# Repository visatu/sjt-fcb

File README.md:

View this project on [CADLAB.io](https://cadlab.io/project/25264).

**PRELIMINARY DESIGN - NOT TESTED - YET**

# sjt-fcb

Drone flight controller designed for hobbyist use. Designed as a part of an embedded design course.

## Features

| Component     | Desc                                                                                                                                                                                                |
| ------------- | --------------------------------------------------------------------------------------------------------------------------------------------------------------------------------------------------- |
| CPU           | [ST STM32F411CEU6](https://www.st.com/resource/en/datasheet/stm32f411ce.pdf)                                                                                                                        |
| IMU           | [ST LSM6DS3](https://content.arduino.cc/assets/st_imu_lsm6ds3_datasheet.pdf)                                                                                                                        |
| Onboard flash | 128 Mb SPI NOR                                                                                                                                                                                      |
| RF Module     | [SiLabs SI4432](https://www.silabs.com/documents/public/data-sheets/Si4430-31-32.pdf) based 315 - 915 MHz [module](https://datasheet.lcsc.com/lcsc/1912111437_DreamLNK-DL-RTS4432-433M_C381165.pdf) |
| Barometer     | [Infineon DPS310](https://www.infineon.com/dgdl/Infineon-DPS310-DataSheet-v01_02-EN.pdf?fileId=5546d462576f34750157750826c42242)                                                                    |
| Magnetometer  | [QST QMC5883L ](https://datasheet.lcsc.com/lcsc/2012221837_QST-QMC5883L_C976032.pdf)                                                                                                                |
|               |                                                                                                                                                                                                     |

- Designed to connect to a
[RaceStar 35A](https://www.racerstar.com/Anniversary-Special-Edition-Racerstar-REV35-35A-BLheli_S-3-6S-4-In-1-ESC-Built-in-Current-Sensor-for-RC-Drone-p-254.html) ESC
- 2.0 mm pitch connectors for external I/O
  - I2C
  - UART
  - 2 x 5V Analog input
  - 1 x 3V Analog input
  - 2 x GPIO
- USB 2.0 connection
- Onboard buzzer
- User programmable button :)

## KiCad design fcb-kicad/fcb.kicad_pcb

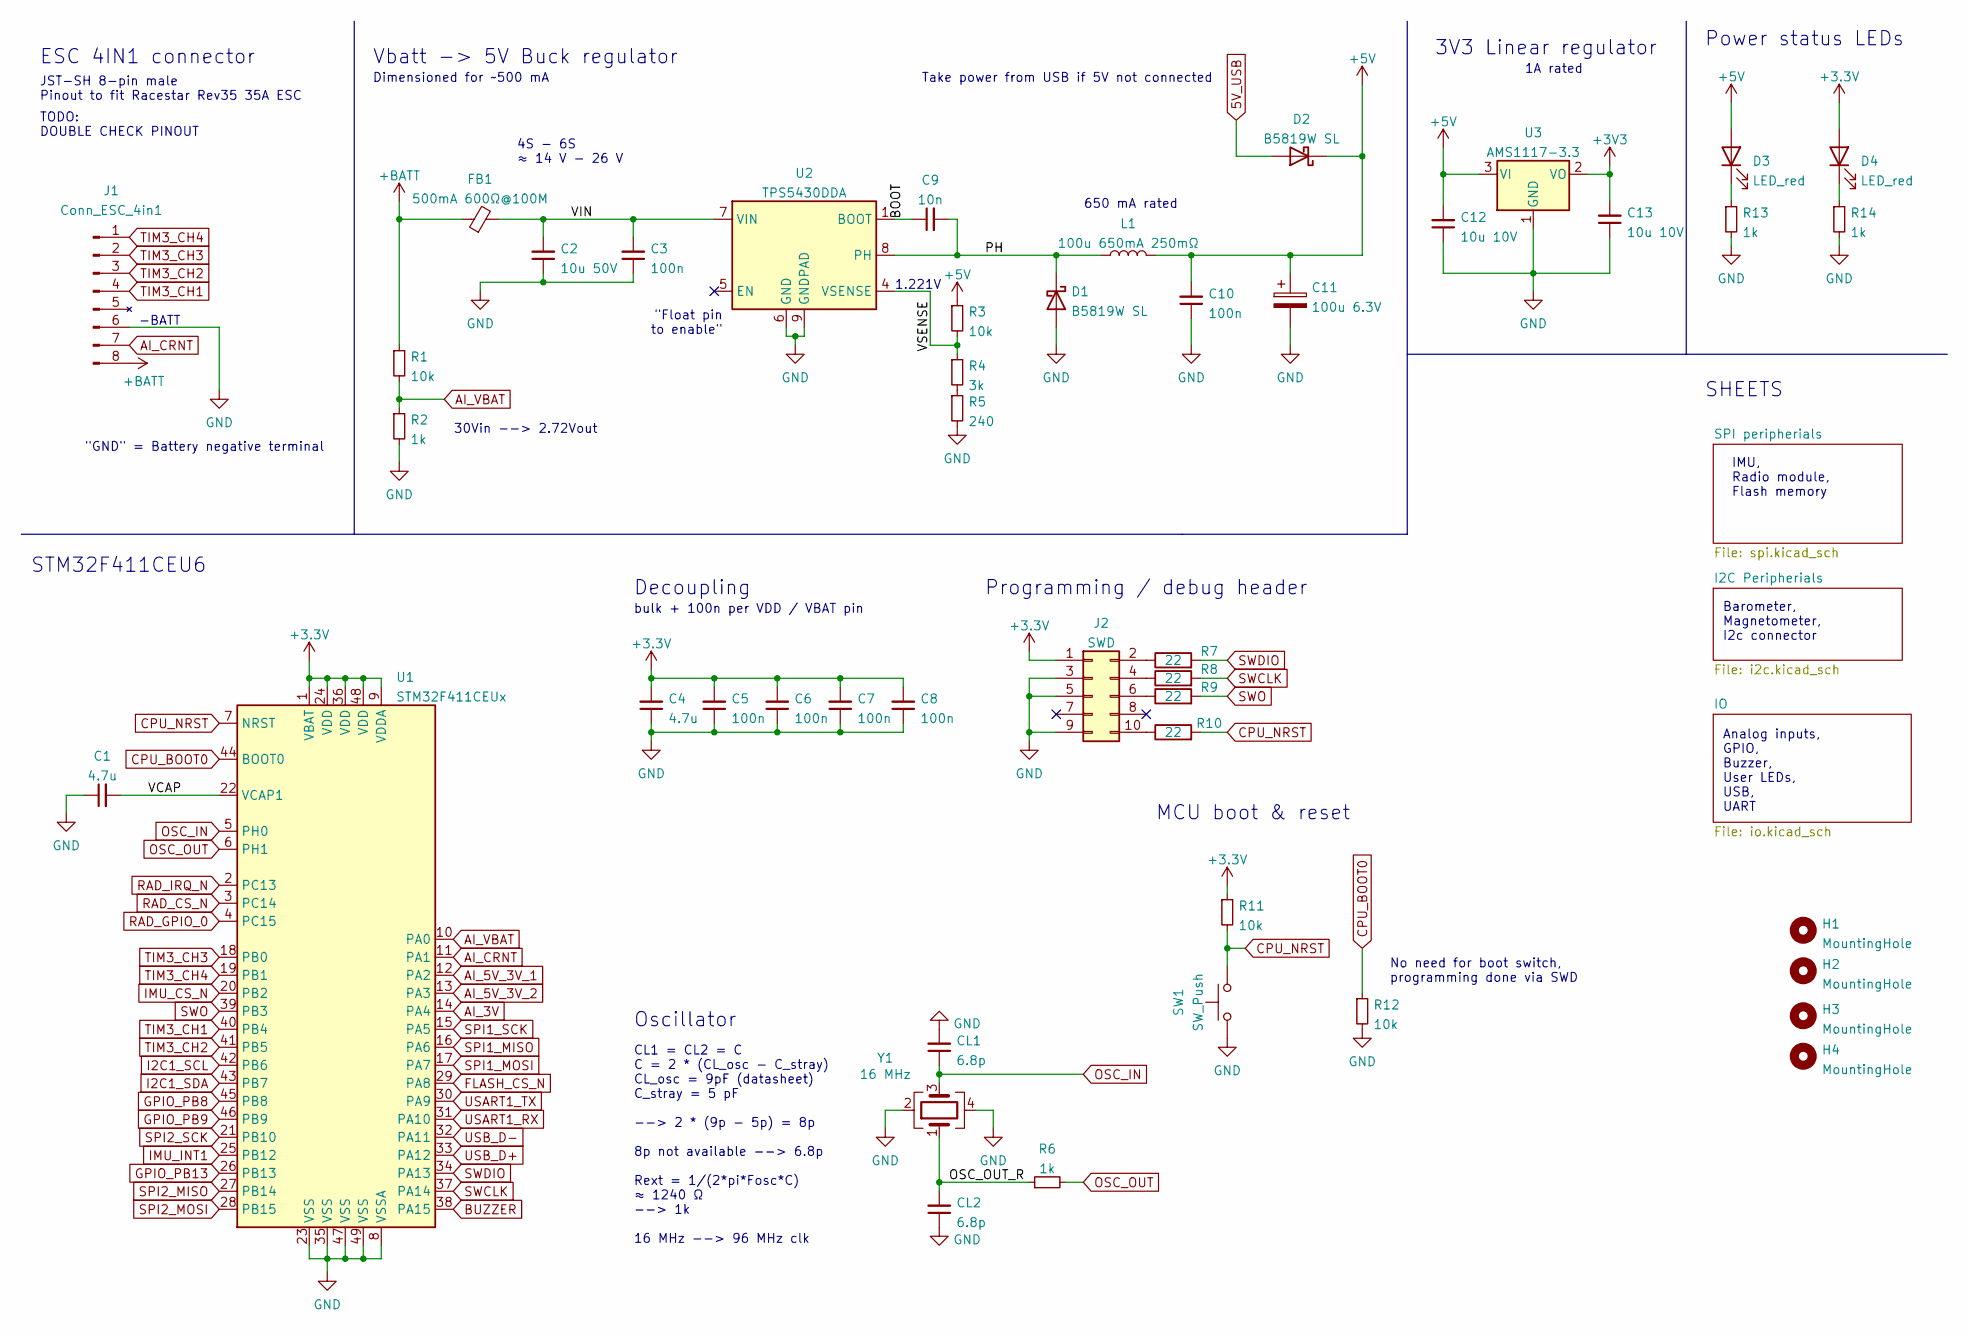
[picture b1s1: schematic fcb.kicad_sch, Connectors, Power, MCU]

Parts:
C1, C4: 4.7u; C_0603_1608Metric; LCSC C19666
C2: 10u 50V; C_1206_3216Metric; LCSC C89632
C3, C5, C6, C7, C8, C10: 100n; C_0603_1608Metric; LCSC C14663
C9: 10n; C_0603_1608Metric; LCSC C57112
C11: 100u 6.3V; CP_EIA-3528-15_AVX-H_Pad1.50x2.35mm_HandSolder; LCSC C16133
C12, C13: 10u 10V; C_0603_1608Metric; LCSC C19702
CL1, CL2: 6.8p; C_0603_1608Metric; LCSC C1679
D1, D2: B5819W SL; D_SOD-123; LCSC C8598
D3, D4: LED_red; LED_0603_1608Metric; LCSC C84263
FB1: 500mA 600Ω@100M; C_0805_2012Metric; LCSC C1017
H1, H2, H3, H4: MountingHole; MountingHole_3.2mm_M3_DIN965_Pad
J1: Conn_ESC_4in1; JST_SH_SM08B-SRSS-TB_1x08-1MP_P1.00mm_Horizontal; LCSC C49633
J2: SWD; PinHeader_2x05_P1.27mm_Vertical; LCSC C2895038
L1: 100u 650mA 250mΩ; L_7.3x7.3_H4.5; LCSC C254876
R1, R3, R11, R12: 10k; R_0603_1608Metric; LCSC C25804
R2, R6, R13, R14: 1k; R_0603_1608Metric; LCSC C21190
R4: 3k; R_0603_1608Metric; LCSC C4211
R5: 240; R_0603_1608Metric; LCSC C23350
R7, R8, R9, R10: 22; R_0603_1608Metric; LCSC C23345
SW1: SW_Push; Button-2.9x4.0mm-SMD; LCSC C720477
U1: STM32F411CEUx; QFN-48-1EP_7x7mm_P0.5mm_EP5.6x5.6mm; LCSC C60420
U2: TPS5430DDA; TI_SO-PowerPAD-8_ThermalVias; LCSC C9864
U3: AMS1117-3.3; SOT-223-3_TabPin2; LCSC C6186
Y1: 16 MHz; Crystal_SMD_3225-4Pin_3.2x2.5mm; LCSC C13738

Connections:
5V_USB: D2.2 (A); also elsewhere on the board
+5V: C10.2, C11.1, C12.2, D2.1 (K), D3.2 (A), L1.2, R3.1, U3.3 (VI); also elsewhere on the board
+BATT: FB1.1, J1.8 (VBAT), R1.1
/BOOT: C9.1, U2.1 (BOOT)
/OSC_OUT_R: CL2.2, R6.1, Y1.1
/PH: C9.2, D1.1 (K), L1.1, U2.8 (PH)
/VCAP: C1.2, U1.22 (VCAP1)
/VIN: C2.2, C3.2, FB1.2, U2.7 (VIN)
/VSENSE: R3.2, R4.1, U2.4 (VSENSE)
AI_3V: U1.14 (PA4); also elsewhere on the board
AI_5V_3V_1: U1.12 (PA2); also elsewhere on the board
AI_5V_3V_2: U1.13 (PA3); also elsewhere on the board
AI_CRNT: J1.7 (CRNT), U1.11 (PA1)
AI_VBAT: R1.2, R2.1, U1.10 (PA0)
BUZZER: U1.38 (PA15); also elsewhere on the board
CPU_BOOT0: R12.1, U1.44 (BOOT0)
CPU_NRST: R10.2, R11.2, SW1.2, U1.7 (NRST)
FLASH_CS_N: U1.29 (PA8); also elsewhere on the board
GND: C1.1, C2.1, C3.1, C4.1, C5.1, C6.1, C7.1, C8.1, C10.1, C11.2, C12.1, C13.1, CL1.2, CL2.1, D1.2 (A), J1.6 (GND), J2.3, J2.5, J2.9, R2.2, R5.2, R12.2, R13.2, R14.2, SW1.1, U1.8 (VSSA), U1.23 (VSS), U1.35 (VSS), U1.47 (VSS), U1.49 (VSS), U2.6 (GND), U2.9 (GNDPAD), U3.1 (GND), Y1.2, Y1.4; also elsewhere on the board
GPIO_PB8: U1.45 (PB8); also elsewhere on the board
GPIO_PB9: U1.46 (PB9); also elsewhere on the board
GPIO_PB13: U1.26 (PB13); also elsewhere on the board
I2C1_SCL: U1.42 (PB6); also elsewhere on the board
I2C1_SDA: U1.43 (PB7); also elsewhere on the board
IMU_CS_N: U1.20 (PB2); also elsewhere on the board
IMU_INT1: U1.25 (PB12); also elsewhere on the board
unnamed: D3.1 (K), R13.1
unnamed: D4.1 (K), R14.1
unnamed: J2.2, R7.1
unnamed: J2.4, R8.1
unnamed: J2.6, R9.1
unnamed: J2.10, R10.1
unnamed: R4.2, R5.1
OSC_IN: CL1.1, U1.5 (PH0), Y1.3
OSC_OUT: R6.2, U1.6 (PH1)
RAD_CS_N: U1.3 (PC14); also elsewhere on the board
RAD_GPIO_0: U1.4 (PC15); also elsewhere on the board
RAD_IRQ_N: U1.2 (PC13); also elsewhere on the board
SPI1_MISO: U1.16 (PA6); also elsewhere on the board
SPI1_MOSI: U1.17 (PA7); also elsewhere on the board
SPI1_SCK: U1.15 (PA5); also elsewhere on the board
SPI2_MISO: U1.27 (PB14); also elsewhere on the board
SPI2_MOSI: U1.28 (PB15); also elsewhere on the board
SPI2_SCK: U1.21 (PB10); also elsewhere on the board
SWCLK: R8.2, U1.37 (PA14)
SWDIO: R7.2, U1.34 (PA13)
SWO: R9.2, U1.39 (PB3)
TIM3_CH1: J1.4 (IN1), U1.40 (PB4)
TIM3_CH2: J1.3 (IN2), U1.41 (PB5)
TIM3_CH3: J1.2 (IN3), U1.18 (PB0)
TIM3_CH4: J1.1 (IN4), U1.19 (PB1)
USART1_RX: U1.31 (PA10); also elsewhere on the board
USART1_TX: U1.30 (PA9); also elsewhere on the board
USB_D+: U1.33 (PA12); also elsewhere on the board
USB_D-: U1.32 (PA11); also elsewhere on the board

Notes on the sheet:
Power status LEDs
MCU boot & reset
Barometer, Magnetometer, I2c connector
Vbatt -> 5V Buck regulator
STM32F411CEU6
JST-SH 8-pin male Pinout to fit Racestar Rev35 35A ESC
30Vin --> 2.72Vout
Programming / debug header
1A rated
3V3 Linear regulator
Decoupling
"Float pin to enable"
Take power from USB if 5V not connected
-BATT
Dimensioned for ~500 mA
"GND" = Battery negative terminal
ESC 4IN1 connector
Analog inputs, GPIO, Buzzer, User LEDs, USB, UART
SHEETS
Oscillator
650 mA rated
4S - 6S ≈ 14 V - 26 V
bulk + 100n per VDD / VBAT pin
1.221V
CL1 = CL2 = C C = 2 * (CL_osc - C_stray) CL_osc = 9pF (datasheet) C_stray = 5 pF --> 2 * (9p - 5p) = 8p 8p not available --> 6.8p Rext = 1/(2*pi*Fosc*C) ≈ 1240 Ω --> 1k 16 MHz --> 96 MHz clk
No need for boot switch, programming done via SWD
IMU, Radio module, Flash memory
TODO: DOUBLE CHECK PINOUT

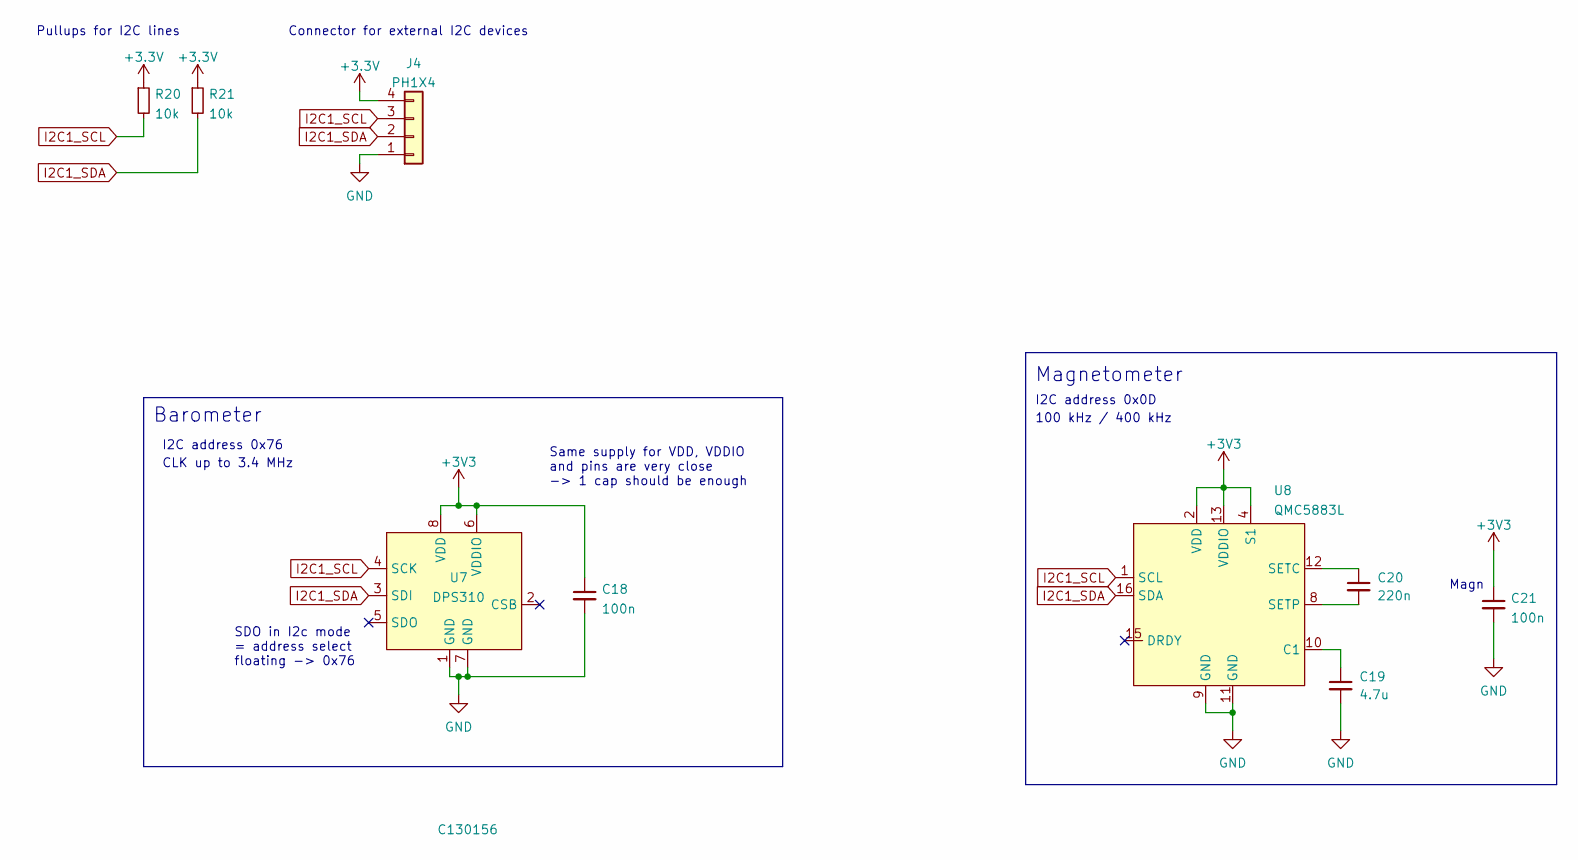
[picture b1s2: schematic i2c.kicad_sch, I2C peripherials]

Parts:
C18, C21: 100n; C_0603_1608Metric; LCSC C14663
C19: 4.7u; C_0603_1608Metric; LCSC C19666
C20: 220n; C_0603_1608Metric; LCSC C21120
J4: PH1X4; PinHeader_1x04_P2.00mm_Vertical; LCSC C388723
R20, R21: 10k; R_0603_1608Metric; LCSC C25804
U7: DPS310; PG-VLGA-8-1; LCSC C130156
U8: QMC5883L; LCSC C976032

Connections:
GND: C18.2, C19.2, C21.2, J4.1, U7.1 (GND), U7.7 (GND), U8.9 (GND), U8.11 (GND); also elsewhere on the board
I2C1_SCL: J4.3, R20.2, U7.4 (SCK), U8.1 (SCL); also elsewhere on the board
I2C1_SDA: J4.2, R21.2, U7.3 (SDI), U8.16 (SDA); also elsewhere on the board
unnamed: C19.1, U8.10 (C1)
unnamed: C20.1, U8.12 (SETC)
unnamed: C20.2, U8.8 (SETP)

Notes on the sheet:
Pullups for I2C lines
SDO in I2c mode = address select floating -> 0x76
CLK up to 3.4 MHz
I2C address 0x0D
Connector for external I2C devices
Magnetometer
100 kHz / 400 kHz
Same supply for VDD, VDDIO and pins are very close -> 1 cap should be enough
I2C address 0x76
Barometer
Magn

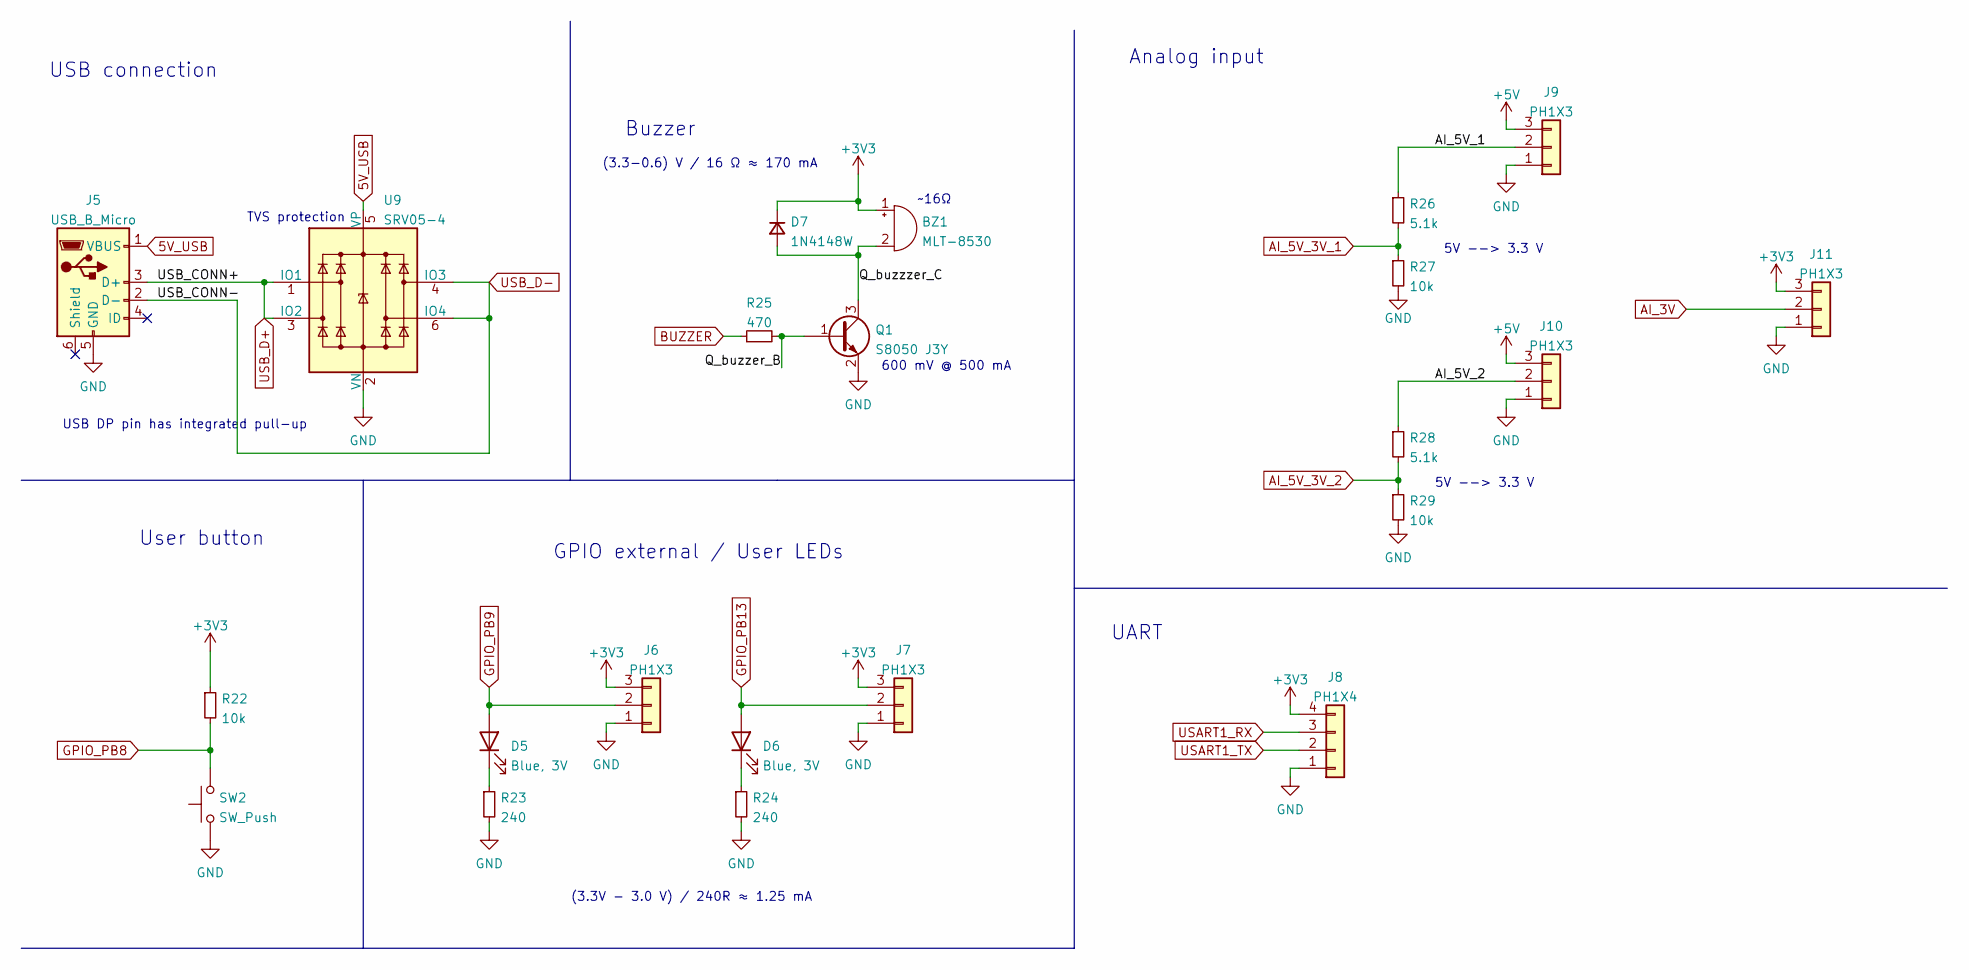
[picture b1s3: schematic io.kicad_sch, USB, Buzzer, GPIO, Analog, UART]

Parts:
BZ1: MLT-8530; MLT-8350; LCSC C94599
D5, D6: Blue, 3V; LED_0603_1608Metric; LCSC C72041
D7: 1N4148W; D_SOD-123; LCSC C81598
J5: USB_B_Micro; MICRO-USB-SMD_U254-051T-4BH83-F1S; LCSC C397452
J6, J7, J9, J10, J11: PH1X3; PinHeader_1x03_P2.00mm_Vertical; LCSC C571312
J8: PH1X4; PinHeader_1x04_P2.00mm_Vertical; LCSC C388723
Q1: S8050 J3Y; SOT-23; LCSC C2146
R22, R27, R29: 10k; R_0603_1608Metric; LCSC C25804
R23, R24: 240; R_0603_1608Metric; LCSC C23350
R25: 470; R_0603_1608Metric; LCSC C23179
R26, R28: 5.1k; R_0603_1608Metric; LCSC C23186
SW2: SW_Push; Button-2.9x4.0mm-SMD; LCSC C720477
U9: SRV05-4; SOT-23-6; LCSC C85364

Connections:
5V_USB: J5.1 (VBUS), U9.5 (VP); also elsewhere on the board
+5V: J9.3, J10.3; also elsewhere on the board
/IO/AI_5V_1: J9.2, R26.1
/IO/AI_5V_2: J10.2, R28.1
/IO/Q_buzzer_B: Q1.1 (B), R25.2
/IO/Q_buzzzer_C: BZ1.2 (+), D7.2 (A), Q1.3 (C)
AI_3V: J11.2; also elsewhere on the board
AI_5V_3V_1: R26.2, R27.1; also elsewhere on the board
AI_5V_3V_2: R28.2, R29.1; also elsewhere on the board
BUZZER: R25.1; also elsewhere on the board
GND: J5.5 (GND), J6.1, J7.1, J8.1, J9.1, J10.1, J11.1, Q1.2 (E), R23.2, R24.2, R27.2, R29.2, SW2.1, U9.2 (VN); also elsewhere on the board
GPIO_PB8: R22.2, SW2.2; also elsewhere on the board
GPIO_PB9: D5.2 (A), J6.2; also elsewhere on the board
GPIO_PB13: D6.2 (A), J7.2; also elsewhere on the board
unnamed: D5.1 (K), R23.1
unnamed: D6.1 (K), R24.1
USART1_RX: J8.3; also elsewhere on the board
USART1_TX: J8.2; also elsewhere on the board
USB_D+: J5.3 (D+), U9.1 (IO1), U9.3 (IO2); also elsewhere on the board
USB_D-: J5.2 (D-), U9.4 (IO3), U9.6 (IO4); also elsewhere on the board

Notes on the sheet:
USB connection
User button
(3.3V - 3.0 V) / 240R ≈ 1.25 mA
USB DP pin has integrated pull-up
Analog input
Buzzer
GPIO external / User LEDs
5V --> 3.3 V
UART
TVS protection
~16Ω
600 mV @ 500 mA
(3.3-0.6) V / 16 Ω ≈ 170 mA

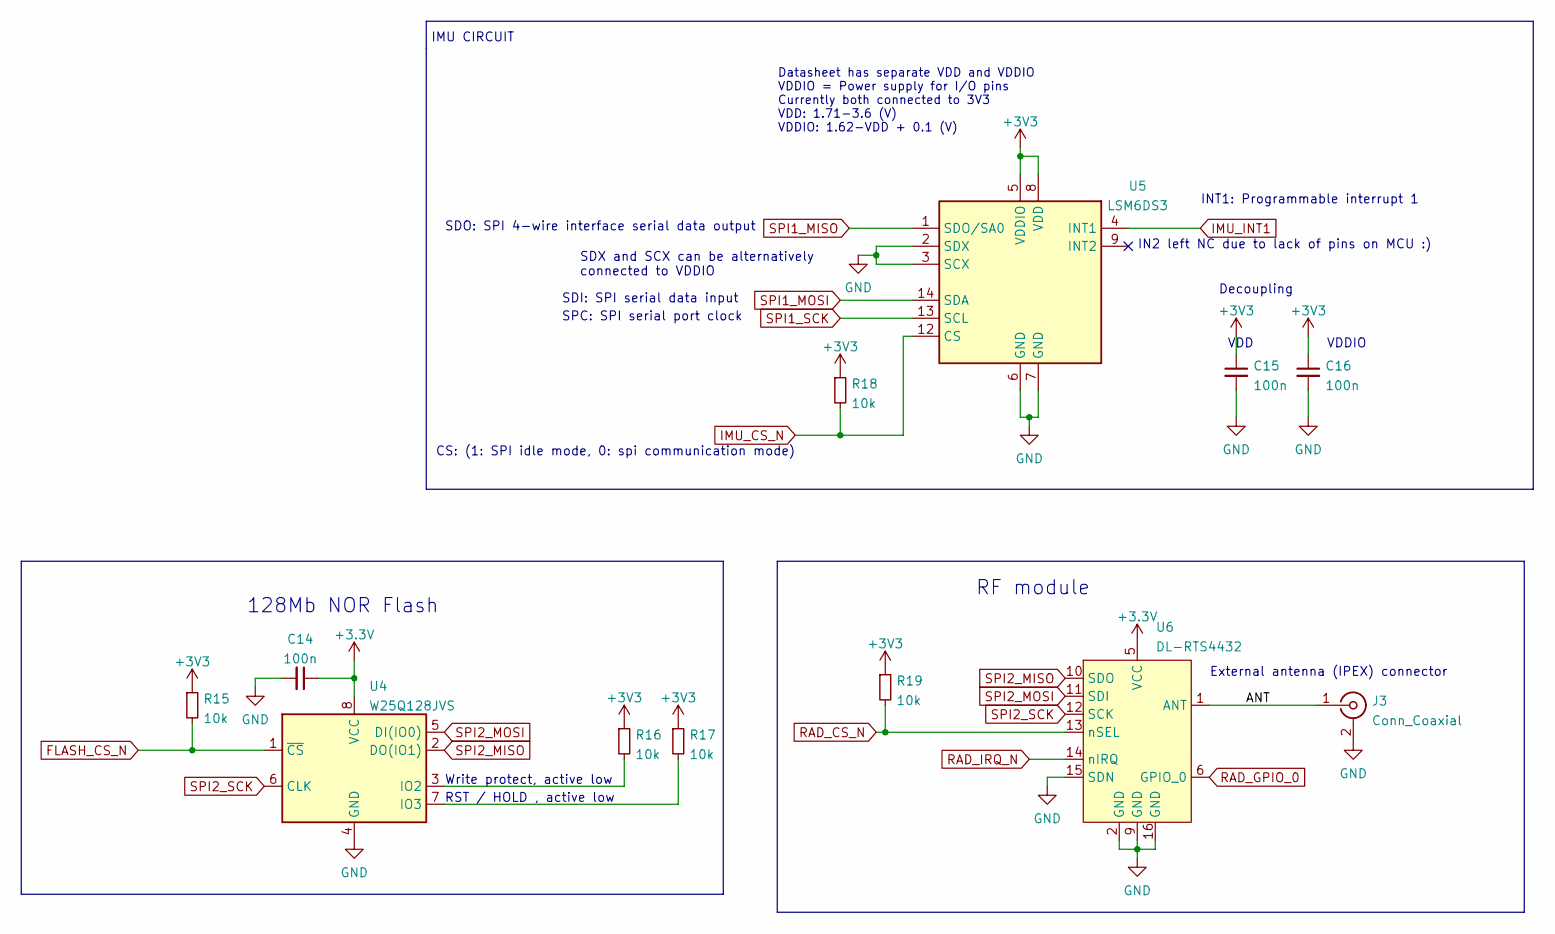
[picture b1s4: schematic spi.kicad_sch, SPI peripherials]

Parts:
C14, C15, C16: 100n; C_0603_1608Metric; LCSC C14663
J3: Conn_Coaxial; KH-IPEX-K501-29; LCSC C411563
R15, R16, R17, R18, R19: 10k; R_0603_1608Metric; LCSC C25804
U4: W25Q128JVS; SOIC-8_5.23x5.23mm_P1.27mm; LCSC C97521
U5: LSM6DS3; LGA-14_3x2.5mm_P0.5mm_LayoutBorder3x4y; LCSC C95230
U6: DL-RTS4432; DL-RTS4432_board; LCSC C381165

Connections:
/SPI peripherials/ANT: J3.1 (In), U6.1 (ANT)
FLASH_CS_N: R15.2, U4.1 (~CS); also elsewhere on the board
GND: C14.2, C15.2, C16.2, J3.2 (Ext), U4.4 (GND), U5.2 (SDX), U5.3 (SCX), U5.6 (GND), U5.7 (GND), U6.2 (GND), U6.9 (GND), U6.15 (SDN), U6.16 (GND); also elsewhere on the board
IMU_CS_N: R18.2, U5.12 (CS); also elsewhere on the board
IMU_INT1: U5.4 (INT1); also elsewhere on the board
unnamed: R16.2, U4.3 (IO2)
unnamed: R17.2, U4.7 (IO3)
RAD_CS_N: R19.2, U6.13 (nSEL); also elsewhere on the board
RAD_GPIO_0: U6.6 (GPIO_0); also elsewhere on the board
RAD_IRQ_N: U6.14 (nIRQ); also elsewhere on the board
SPI1_MISO: U5.1 (SDO/SA0); also elsewhere on the board
SPI1_MOSI: U5.14 (SDA); also elsewhere on the board
SPI1_SCK: U5.13 (SCL); also elsewhere on the board
SPI2_MISO: U4.2 (DO(IO1)), U6.10 (SDO); also elsewhere on the board
SPI2_MOSI: U4.5 (DI(IO0)), U6.11 (SDI); also elsewhere on the board
SPI2_SCK: U4.6 (CLK), U6.12 (SCK); also elsewhere on the board

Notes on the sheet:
Write protect, active low
CS: (1: SPI idle mode, 0: spi communication mode)
SDO: SPI 4-wire interface serial data output
RST / HOLD , active low
Decoupling
SDI: SPI serial data input
SDX and SCX can be alternatively connected to VDDIO
128Mb NOR Flash
IMU CIRCUIT
VDDIO
IN2 left NC due to lack of pins on MCU :)
External antenna (IPEX) connector
SPC: SPI serial port clock
Datasheet has separate VDD and VDDIO VDDIO = Power supply for I/O pins Currently both connected to 3V3 VDD: 1.71-3.6 (V) VDDIO: 1.62-VDD + 0.1 (V)
VDD
RF module
INT1: Programmable interrupt 1

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
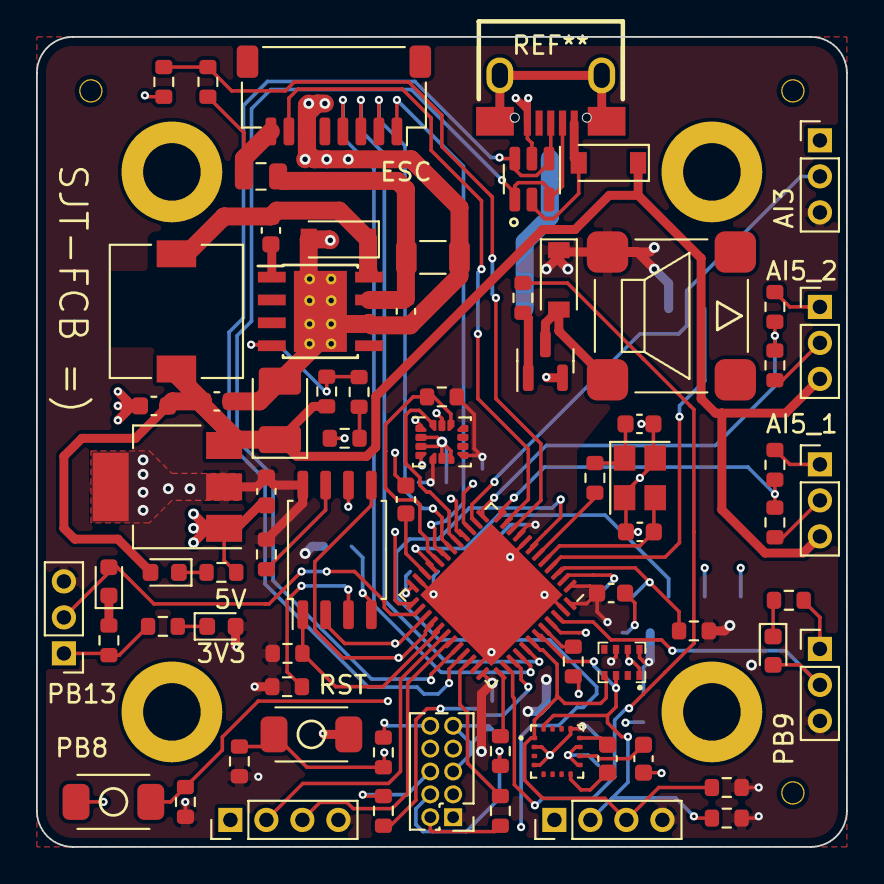
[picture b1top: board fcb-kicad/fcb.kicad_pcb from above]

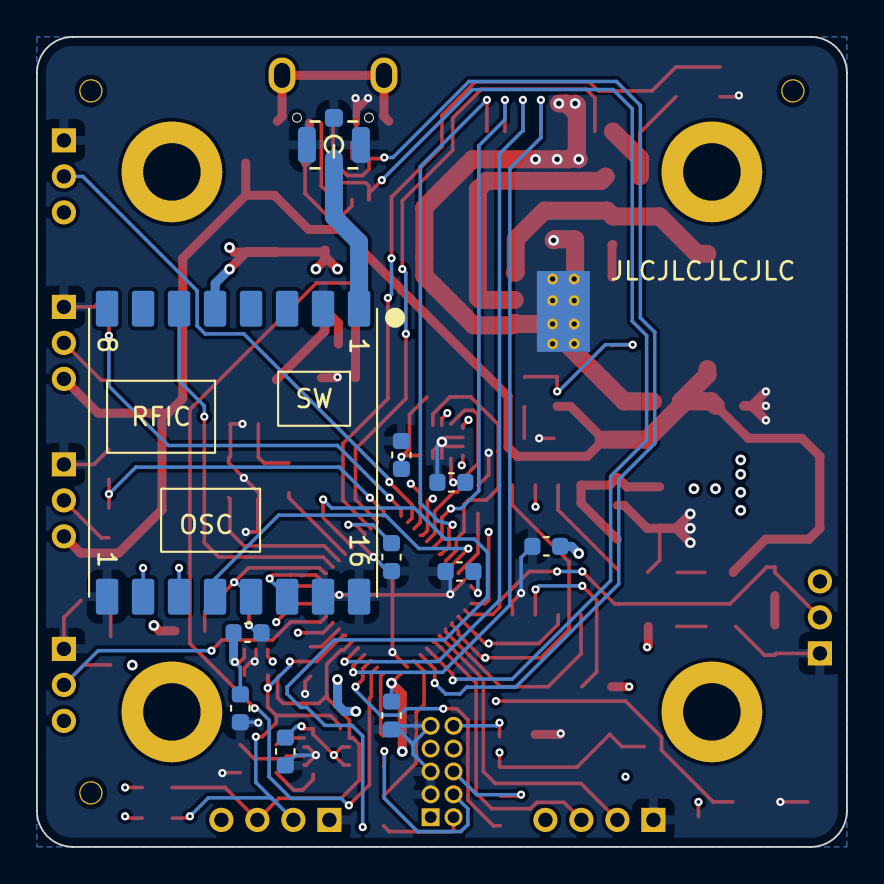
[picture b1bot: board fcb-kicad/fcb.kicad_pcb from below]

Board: 4 copper layers, 45.0 x 45.0 mm, 92 parts (11 on the bottom side), 68 nets.

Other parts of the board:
T1, T2, T3: JLCPCB_NPTH

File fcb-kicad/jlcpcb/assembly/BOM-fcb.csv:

Comment,Designator,Footprint,LCSC
500mA 600Ω@100M,FB1,C_0805_2012Metric,C1017
DPS310,U7,PG-VLGA-8-1,C130156
10u 50V,C2,C_1206_3216Metric,C13585
16 MHz,Y1,Crystal_SMD_3225-4Pin_3.2x2.5mm,C13738
100n,"C10,C14,C15,C16,C18,C21,C3,C5,C6,C7,C8",C_0603_1608Metric,C14663
100u 6.3V,C11,CP_EIA-3528-15_AVX-H_Pad1.50x2.35mm_HandSolder,C16133
6.8p,"CL1,CL2",C_0603_1608Metric,C1679
STM32F411CEUx,U1,QFN-48-1EP_7x7mm_P0.5mm_EP5.6x5.6mm,C190642
4.7u,"C1,C19,C4",C_0603_1608Metric,C19666
10u 10V,"C12,C13",C_0603_1608Metric,C19702
220n,C20,C_0603_1608Metric,C21120
1k,"R13,R14,R2,R6",R_0603_1608Metric,C21190
S8050 J3Y,Q1,SOT-23,C2146
LED_red,"D3,D4",LED_0603_1608Metric,C2286
470,R25,R_0603_1608Metric,C23179
5.1k,"R26,R28",R_0603_1608Metric,C23186
22,"R10,R7,R8,R9",R_0603_1608Metric,C23345
240,"R23,R24,R5",R_0603_1608Metric,C23350
10k,"R1,R11,R12,R15,R16,R17,R18,R19,R20,R21,R22,R27,R29,R3",R_0603_1608Metric,C25804
3k,R4,R_0603_1608Metric,C4211
10n,C9,C_0603_1608Metric,C57112
AMS1117-3.3,U3,SOT-223-3_TabPin2,C6186
"Blue, 3V","D5,D6",LED_0603_1608Metric,C72041
1N4148W,D7,D_SOD-123,C81598
SRV05-4,U9,SOT-23-6,C85364
B5819W SL,"D1,D2",D_SOD-123,C8598
LSM6DS3,U5,LGA-14_3x2.5mm_P0.5mm_LayoutBorder3x4y,C95230
W25Q128JVS,U4,SOIC-8_5.23x5.23mm_P1.27mm,C97521
QMC5883L,U8,QMC5883L,C976032
TPS5430DDA,U2,TI_SO-PowerPAD-8_ThermalVias,C9864

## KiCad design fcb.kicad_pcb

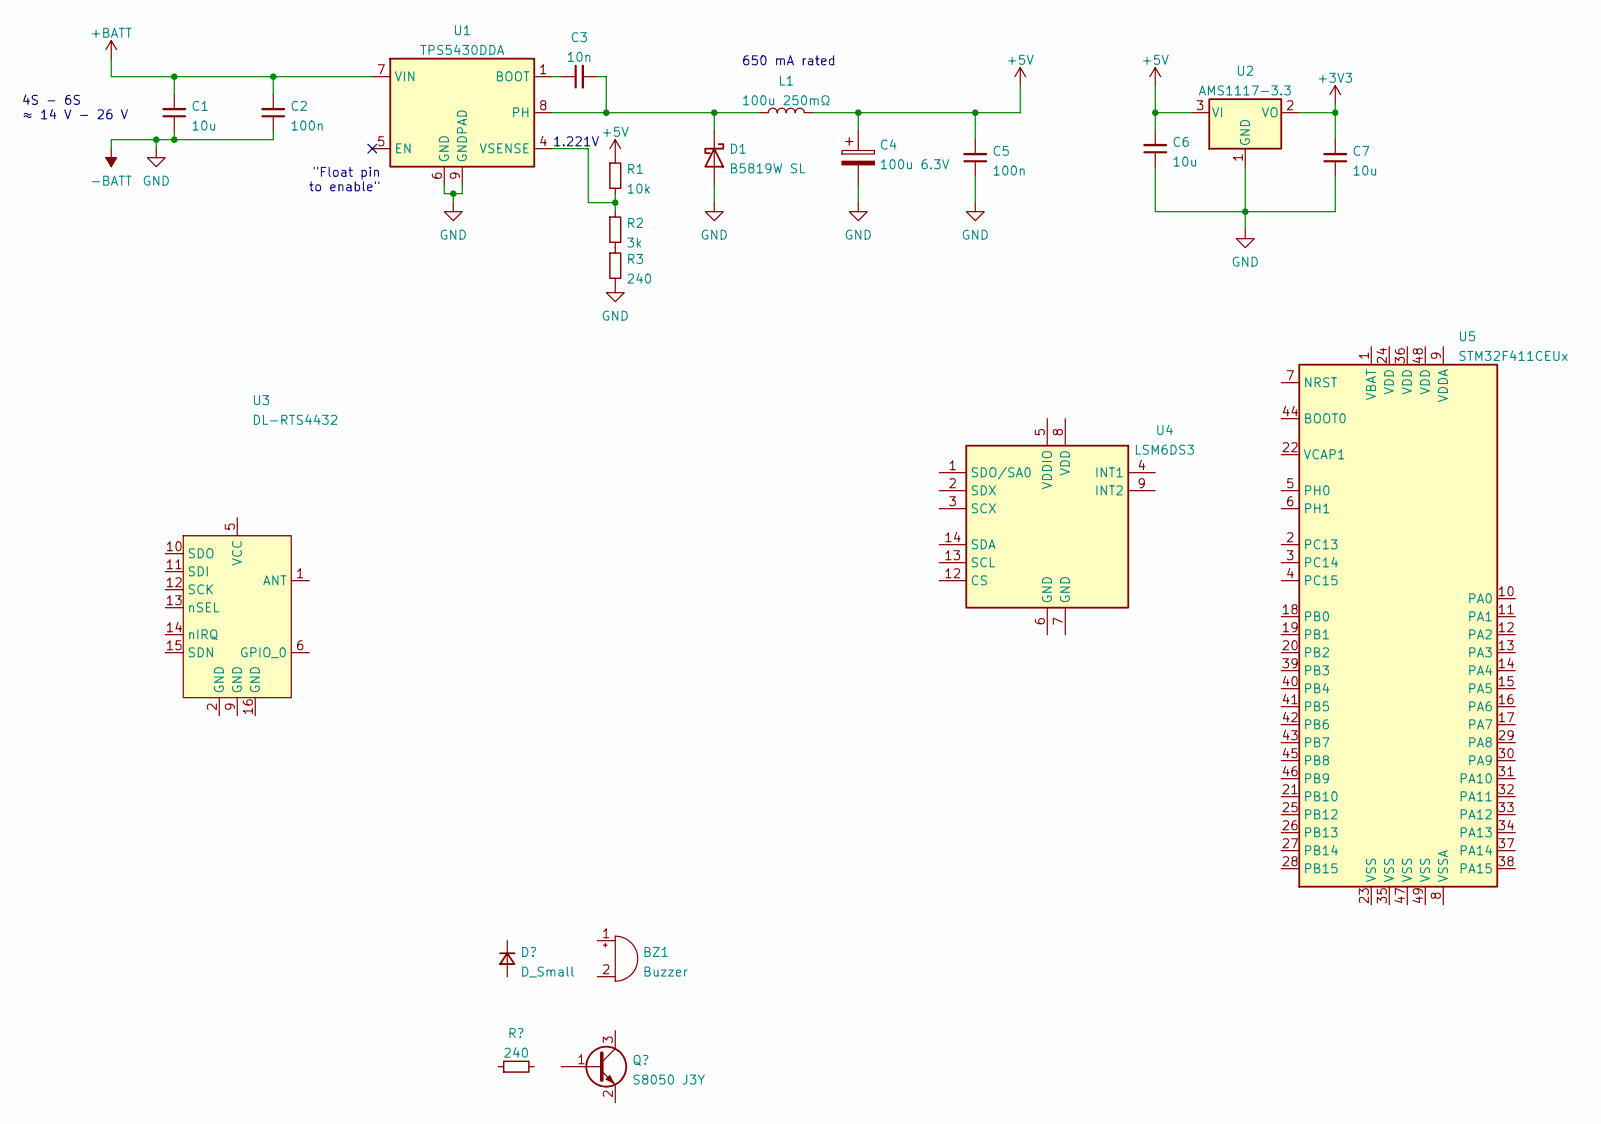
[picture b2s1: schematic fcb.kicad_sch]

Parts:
BZ1: Buzzer; Buzzer_TDK_PS1240P02BT_D12.2mm_H6.5mm
C1, C6, C7: 10u; C_1206_3216Metric_Pad1.33x1.80mm_HandSolder; LCSC C13585
C2, C5: 100n; C_0603_1608Metric_Pad1.08x0.95mm_HandSolder; LCSC C14663
C3: 10n; C_0603_1608Metric; LCSC C57112
C4: 100u 6.3V; CP_EIA-3528-15_AVX-H_Pad1.50x2.35mm_HandSolder; LCSC C16133
D1: B5819W SL; D_SOD-123; LCSC C8598
L1: 100u 250mΩ; L_7.3x7.3_H4.5; LCSC C254876
R1: 10k; R_0603_1608Metric; LCSC C25804
R2: 3k; R_0603_1608Metric; LCSC C4211
R3: 240; R_0603_1608Metric; LCSC C23350
U1: TPS5430DDA; TI_SO-PowerPAD-8_ThermalVias; LCSC C9864
U2: AMS1117-3.3; SOT-223-3_TabPin2; LCSC C6186
U3: DL-RTS4432; DL-RTS4432_board; LCSC C381165
U4: LSM6DS3; LGA-14_3x2.5mm_P0.5mm_LayoutBorder3x4y
U5: STM32F411CEUx; QFN-48-1EP_7x7mm_P0.5mm_EP5.6x5.6mm

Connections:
+3V3: C7.2, U2.2 (VO)
+5V: C4.1, C5.2, C6.2, L1.2, R1.1, U2.3 (VI)
+BATT: C1.2, C2.2, U1.7 (VIN)
-BATT: C1.1, C2.1, C4.2, C5.1, C6.1, C7.1, D1.2 (A), R3.2, U1.6 (GND), U1.9 (GNDPAD), U2.1 (GND)
unnamed: C3.1, U1.1 (BOOT)
unnamed: C3.2, D1.1 (K), L1.1, U1.8 (PH)
unnamed: R1.2, R2.1, U1.4 (VSENSE)
unnamed: R2.2, R3.1

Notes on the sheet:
"Float pin to enable"
650 mA rated
4S - 6S ≈ 14 V - 26 V
1.221V

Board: 4 copper layers, 17 parts (1 on the bottom side), 8 nets, no tracks yet.

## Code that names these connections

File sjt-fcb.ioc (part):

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Mcu.Name=STM32F411C(C-E)Ux
Mcu.Package=UFQFPN48
Mcu.UserName=STM32F411CEUx
PA0-WKUP.GPIOParameters=GPIO_Label
PA0-WKUP.GPIO_Label=AI_VBAT
PA0-WKUP.Signal=ADCx_IN0
PA1.GPIOParameters=GPIO_Label
PA1.GPIO_Label=AI_CRNT
PA1.Signal=ADCx_IN1
PA10.Mode=Asynchronous
PA10.Signal=USART1_RX
PA11.Mode=Device_Only
PA11.Signal=USB_OTG_FS_DM
PA12.Mode=Device_Only
PA12.Signal=USB_OTG_FS_DP
PA13.Mode=Trace_Asynchronous_SW
PA13.Signal=SYS_JTMS-SWDIO
PA14.Mode=Trace_Asynchronous_SW
PA14.Signal=SYS_JTCK-SWCLK
PA15.GPIOParameters=GPIO_Label
PA15.GPIO_Label=BUZZER
PA15.Signal=GPIO_Output
PA2.GPIOParameters=GPIO_Label
PA2.GPIO_Label=AI_5V_1
PA2.Signal=ADCx_IN2
PA3.GPIOParameters=GPIO_Label
PA3.GPIO_Label=AI_5V_2
PA3.Signal=ADCx_IN3
PA4.GPIOParameters=GPIO_Label
PA4.GPIO_Label=AI_3V
PA4.Signal=ADCx_IN4
PA5.Mode=Full_Duplex_Master
PA5.Signal=SPI1_SCK
PA6.Mode=Full_Duplex_Master
PA6.Signal=SPI1_MISO
PA7.Mode=Full_Duplex_Master
PA7.Signal=SPI1_MOSI
PA8.GPIOParameters=GPIO_Label
PA8.GPIO_Label=FLASH_CS_N
PA8.Signal=GPIO_Output
PA9.Mode=Asynchronous
PA9.Signal=USART1_TX
PB0.Signal=S_TIM3_CH3
PB1.Signal=S_TIM3_CH4
PB10.Mode=Full_Duplex_Master
PB10.Signal=SPI2_SCK
PB12.GPIOParameters=GPIO_Label
PB12.GPIO_Label=IMU_INT1
PB12.Signal=GPIO_Input
PB13.Signal=GPIO_Output
PB14.Mode=Full_Duplex_Master
PB14.Signal=SPI2_MISO
PB15.Mode=Full_Duplex_Master
PB15.Signal=SPI2_MOSI
PB2.GPIOParameters=GPIO_Label
PB2.GPIO_Label=IMU_CS
PB2.Signal=GPIO_Output
PB3.Mode=Trace_Asynchronous_SW
PB3.Signal=SYS_JTDO-SWO
PB4.Signal=S_TIM3_CH1
PB5.Signal=S_TIM3_CH2
PB6.Mode=I2C
PB6.Signal=I2C1_SCL
PB7.Mode=I2C
PB7.Signal=I2C1_SDA
PB8.Signal=GPIO_Input
PB9.Signal=GPIO_Input
PC13-ANTI_TAMP.GPIOParameters=GPIO_Label
PC13-ANTI_TAMP.GPIO_Label=RAD_IRQ_N
PC13-ANTI_TAMP.Signal=GPXTI13
PC14-OSC32_IN.GPIOParameters=GPIO_Label
PC14-OSC32_IN.GPIO_Label=RAD_CS_N
PC14-OSC32_IN.Signal=GPIO_Output
PC15-OSC32_OUT.GPIOParameters=GPIO_Label
PC15-OSC32_OUT.GPIO_Label=RAD_GPIO_0
PC15-OSC32_OUT.Signal=GPIO_Output
PH0\ -\ OSC_IN.Mode=HSE-External-Oscillator
PH0\ -\ OSC_IN.Signal=RCC_OSC_IN
PH1\ -\ OSC_OUT.Mode=HSE-External-Oscillator
PH1\ -\ OSC_OUT.Signal=RCC_OSC_OUT
RCC.HSE_VALUE=16000000
RCC.SYSCLKFreq_VALUE=96000000
RCC.SYSCLKSource=RCC_SYSCLKSOURCE_PLLCLK
board=custom

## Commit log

2022-02-28 init
2022-02-28 Backlink to CADLAB.io has been added.
2022-02-28 gitignore kicad template
2022-02-28 alku säätöä.
2022-02-28 Delete fcb-backups directory
    ei näit tänne tarvii :D
2022-02-28 bommit mukaa
2022-03-02 kicad into folder :)
2022-03-02 BMP388 footprint + 3D
2022-03-02 Added BMP388 symbol
2022-03-02 Added magnetometer
2022-03-02 Updated magnetometer circuit
2022-03-02 Added imu circuit
2022-03-02 cpu pins
2022-03-02 hierarchic schemas, paljon muuta kivaa
2022-03-02 magnetometer symbol
2022-03-02 4in1 connector library part, SPI CS pullups, migrate magnetometer cirtuit
2022-03-04 buzzer footprint
2022-03-06 buzzer notes
2022-03-09 Analog inputs, connectors to GPIO
2022-03-15 Schema rev0 done, Layout components grouped
2022-03-16 PCB rev0: "Babby's first Leiska"
2022-03-16 USB diffpair to bottom layer for more continous 3V3 fill
2022-03-28 Less routing on inner layers, fabrication, BOM should be OK
2022-04-08 wider pads for barometer footprint
2022-04-25 Change MCU to STM32F411CCU6
2022-05-16 Interactive HTML BOM
2022-05-16 Include all in iBOM
